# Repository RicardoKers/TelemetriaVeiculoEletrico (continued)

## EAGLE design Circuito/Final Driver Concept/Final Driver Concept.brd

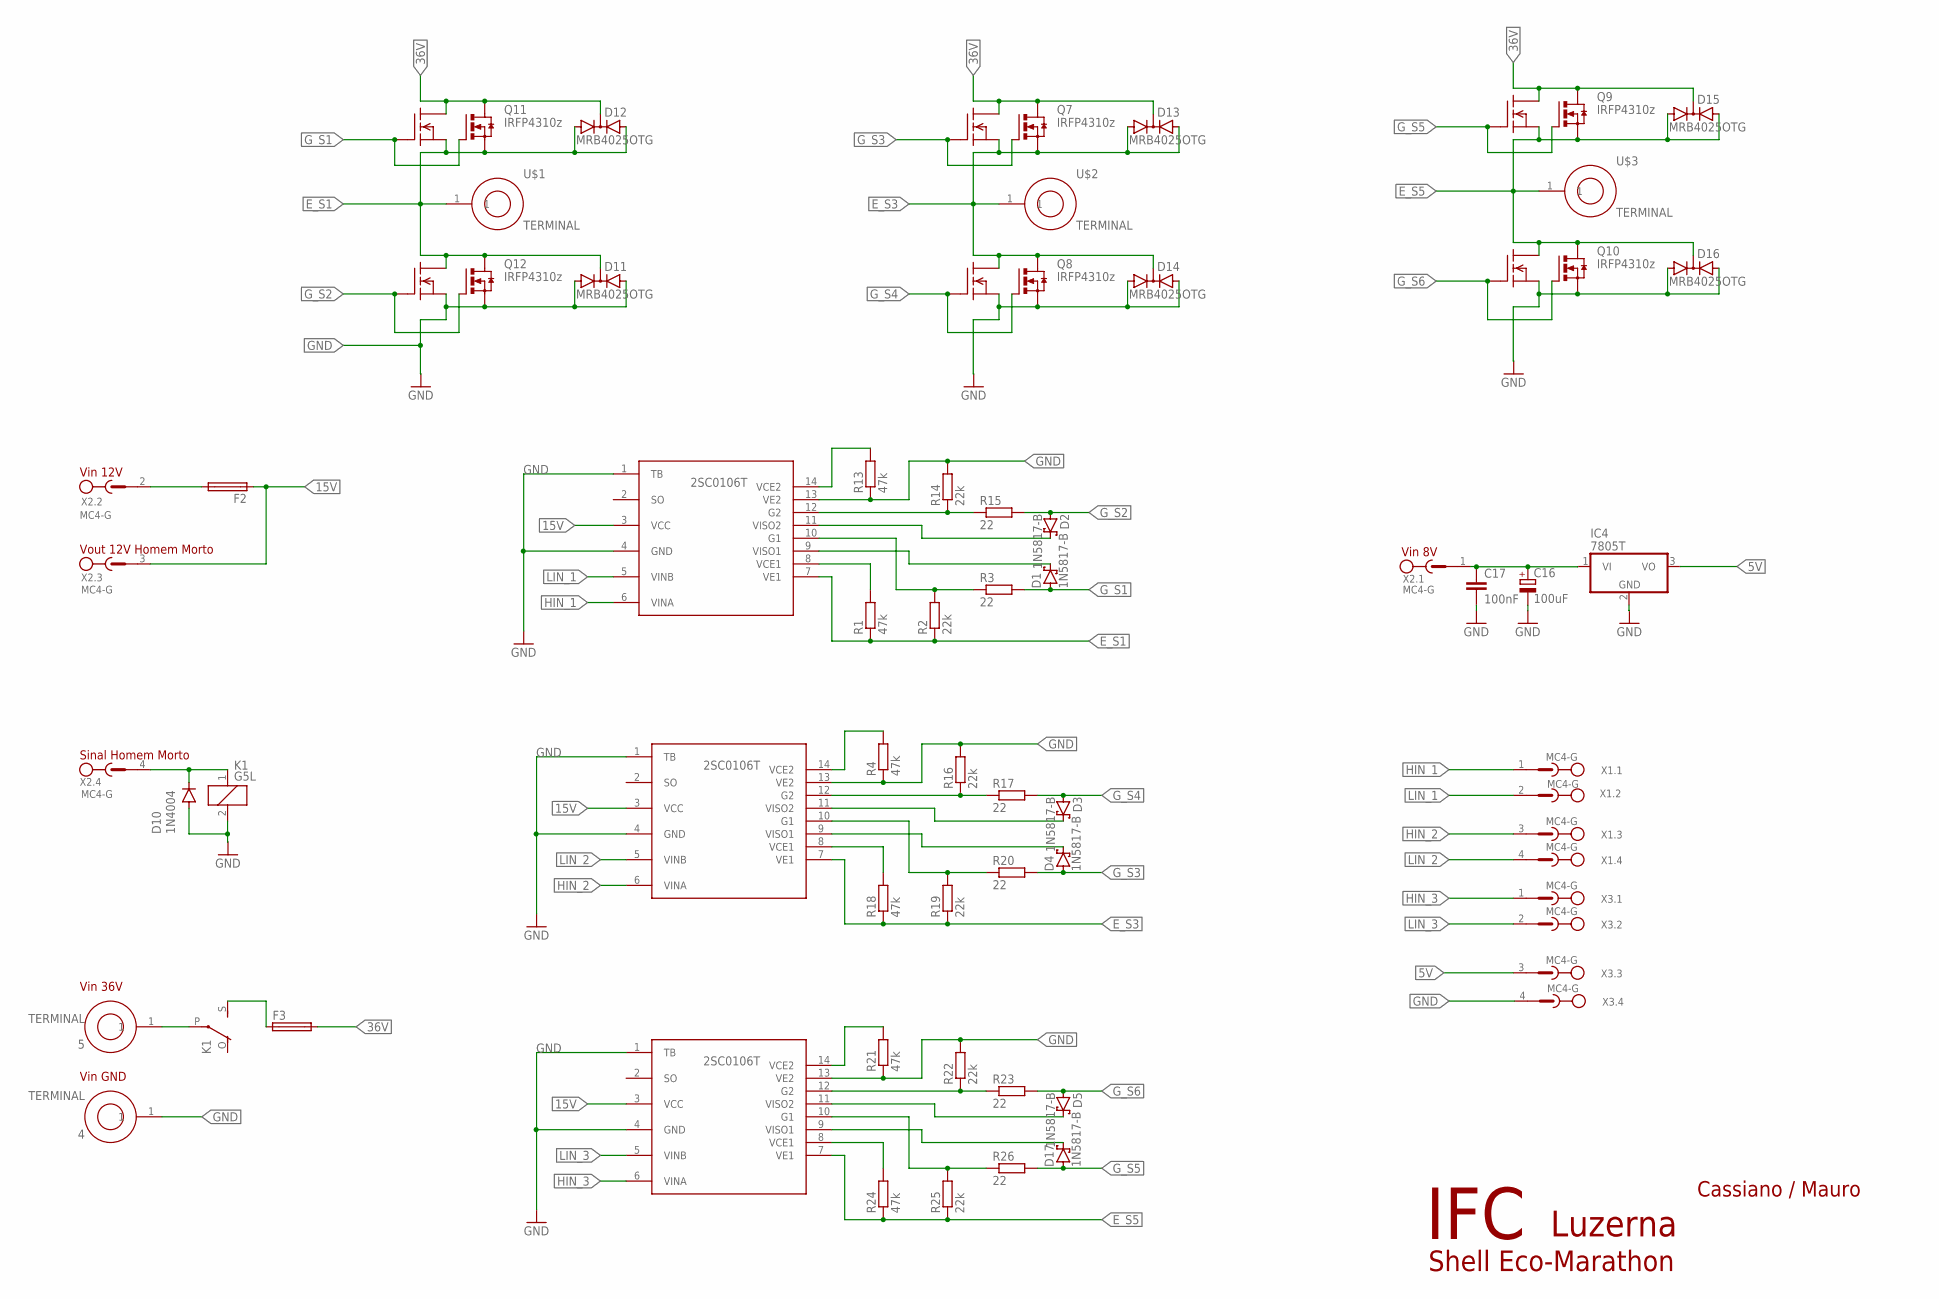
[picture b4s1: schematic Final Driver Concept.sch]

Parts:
4, 5: TERMINAL
C16: 100uF; E2,5-7
C17: 100nF; C050-045X075
D1, D2, D3, D4, D5, D17: 1N5817-B; DO41-7.6
D10: 1N4004; DO41-10
D11, D12, D13, D14, D15, D16: MRB4025OTG; TO220AB
F2, F3: SH22,5A
GATEDRIVER1, GATEDRIVER2, GATEDRIVER3: 2SC0106T1; 2SC0106T
IC4: 7805T; TO220H
K1: G5L; G5LE
Q1, Q2, Q3, Q4, Q5, Q6: IRF540; TO220
Q7, Q8, Q9, Q10, Q11, Q12: IRFP4310z; TO247BH
R1, R4, R13, R18, R21, R24: 47k; 0204/7
R2, R14, R16, R19, R22, R25: 22k; 0204/7
R3, R15, R17, R20, R23, R26: 22; 0204/7
U$1, U$2, U$3: TERMINAL
X1, X2, X3: MC4-G

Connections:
5V: IC4.3 (VO), X3.3
15V: F2.1, GATEDRIVER1.3 (VCC), GATEDRIVER2.3 (VCC), GATEDRIVER3.3 (VCC), X2.3
36V: D12.C, D13.C, D15.C, F3.2, Q1.2 (D), Q3.2 (D), Q5.2 (D), Q7.D, Q9.D, Q11.D
E_S1: D11.C, D12.A1, D12.A2, GATEDRIVER1.7 (VE1), Q1.3 (S), Q2.2 (D), Q11.S, Q12.D, R1.1, R2.1, U$1.1
E_S3: D13.A1, D13.A2, D14.C, GATEDRIVER2.7 (VE1), Q3.3 (S), Q4.2 (D), Q7.S, Q8.D, R18.1, R19.1, U$2.1
E_S5: D15.A1, D15.A2, D16.C, GATEDRIVER3.7 (VE1), Q5.3 (S), Q6.2 (D), Q9.S, Q10.D, R24.1, R25.1, U$3.1
GND: 4.1, C16.-, C17.2, D10.A, D11.A1, D11.A2, D14.A1, D14.A2, D16.A1, D16.A2, GATEDRIVER1.1 (TB), GATEDRIVER1.4 (GND), GATEDRIVER1.13 (VE2), GATEDRIVER2.1 (TB), GATEDRIVER2.4 (GND), GATEDRIVER2.13 (VE2), GATEDRIVER3.1 (TB), GATEDRIVER3.4 (GND), GATEDRIVER3.13 (VE2), IC4.2 (GND), K1.2, Q2.3 (S), Q4.3 (S), Q6.3 (S), Q8.S, Q10.S, Q12.S, R4.1, R13.1, R14.2, R16.2, R21.1, R22.2, X3.4
G_S1: D1.A, Q1.1 (G), Q11.G, R3.2
G_S2: D2.A, Q2.1 (G), Q12.G, R15.2
G_S3: D4.A, Q3.1 (G), Q7.G, R20.2
G_S4: D3.A, Q4.1 (G), Q8.G, R17.2
G_S5: D17.A, Q5.1 (G), Q9.G, R26.2
G_S6: D5.A, Q6.1 (G), Q10.G, R23.2
HIN_1: GATEDRIVER1.6 (VINA), X1.1
HIN_2: GATEDRIVER2.6 (VINA), X1.3
HIN_3: GATEDRIVER3.6 (VINA), X3.1
LIN_1: GATEDRIVER1.5 (VINB), X1.2
LIN_2: GATEDRIVER2.5 (VINB), X1.4
LIN_3: GATEDRIVER3.5 (VINB), X3.2
unnamed: GATEDRIVER2.14 (VCE2), R4.2
unnamed: D1.C, GATEDRIVER1.9 (VISO1)
unnamed: F3.1, K1.S
unnamed: F2.2, X2.2
unnamed: C16.+, C17.1, IC4.1 (VI), X2.1
unnamed: D10.C, K1.1, X2.4
unnamed: 5.1, K1.P
unnamed: GATEDRIVER1.14 (VCE2), R13.2
unnamed: GATEDRIVER1.12 (G2), R14.1, R15.1
unnamed: GATEDRIVER1.8 (VCE1), R1.2
unnamed: D2.C, GATEDRIVER1.11 (VISO2)
unnamed: GATEDRIVER1.10 (G1), R2.2, R3.1
unnamed: GATEDRIVER2.12 (G2), R16.1, R17.1
unnamed: D3.C, GATEDRIVER2.11 (VISO2)
unnamed: GATEDRIVER2.8 (VCE1), R18.2
unnamed: D4.C, GATEDRIVER2.9 (VISO1)
unnamed: GATEDRIVER2.10 (G1), R19.2, R20.1
unnamed: GATEDRIVER3.14 (VCE2), R21.2
unnamed: GATEDRIVER3.12 (G2), R22.1, R23.1
unnamed: D5.C, GATEDRIVER3.11 (VISO2)
unnamed: GATEDRIVER3.8 (VCE1), R24.2
unnamed: D17.C, GATEDRIVER3.9 (VISO1)
unnamed: GATEDRIVER3.10 (G1), R25.2, R26.1

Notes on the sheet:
Vin 8V
Vin 12V
Vout 12V Homem Morto
Sinal Homem Morto
Vin 36V
Vin GND
Shell Eco-Marathon
Cassiano / Mauro
IFC
Luzerna

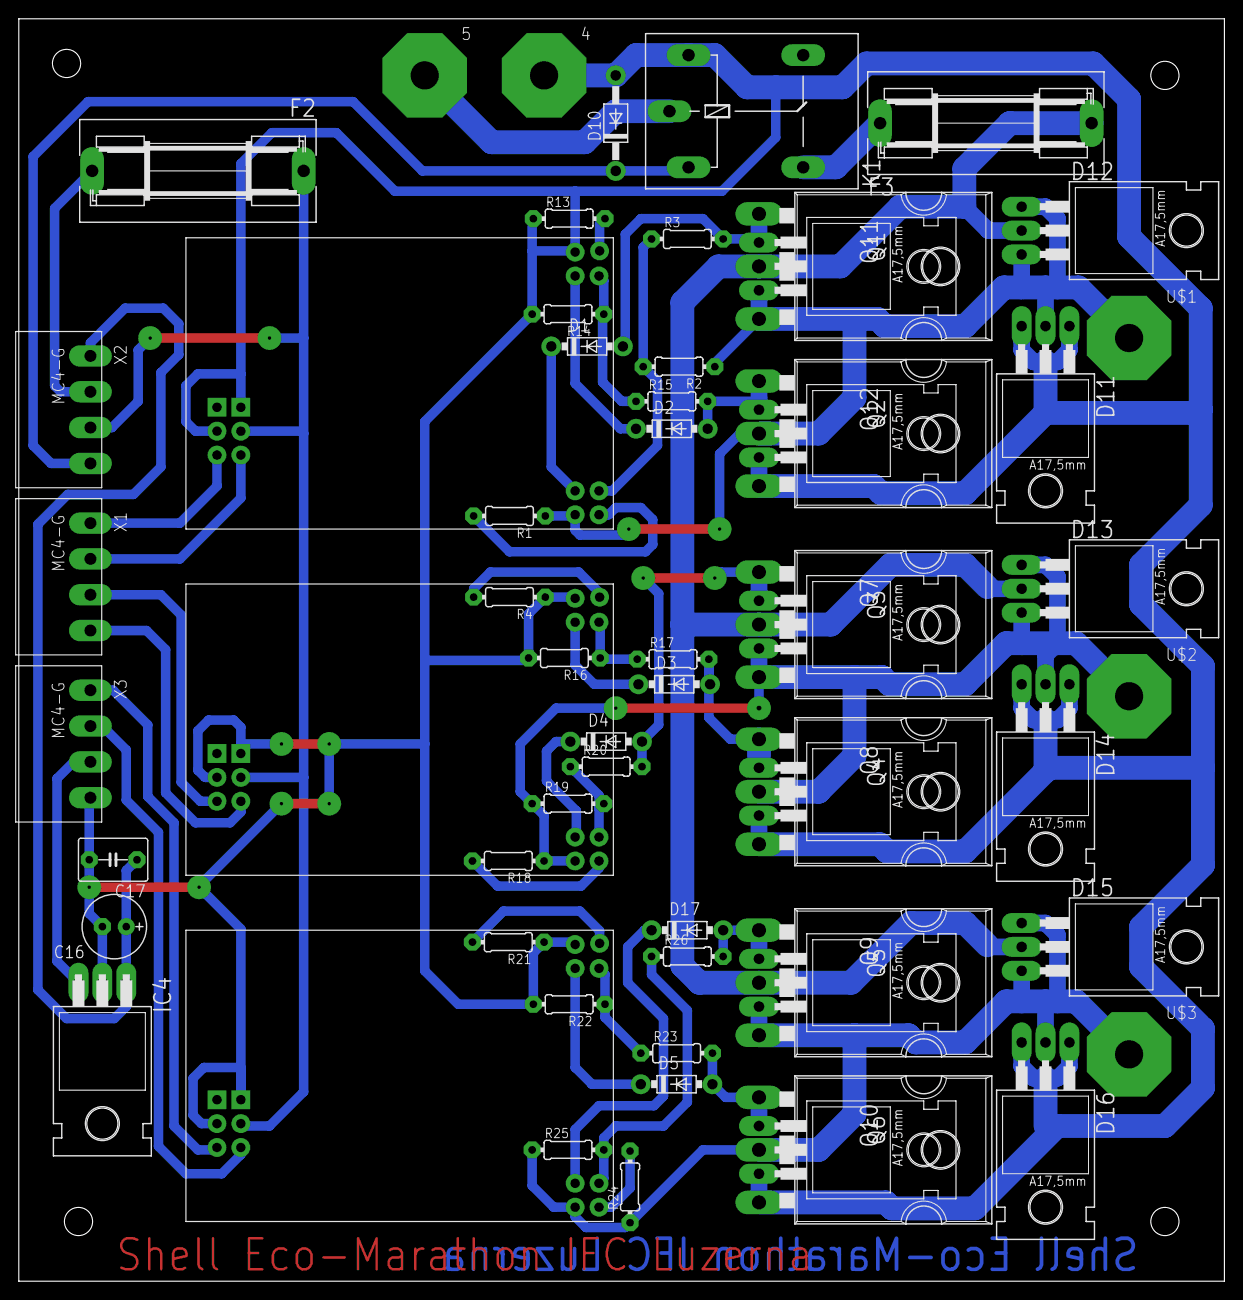
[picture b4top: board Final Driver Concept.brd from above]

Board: 2 copper layers, 128.2 x 134.3 mm, 60 parts (0 on the bottom side), 42 nets.

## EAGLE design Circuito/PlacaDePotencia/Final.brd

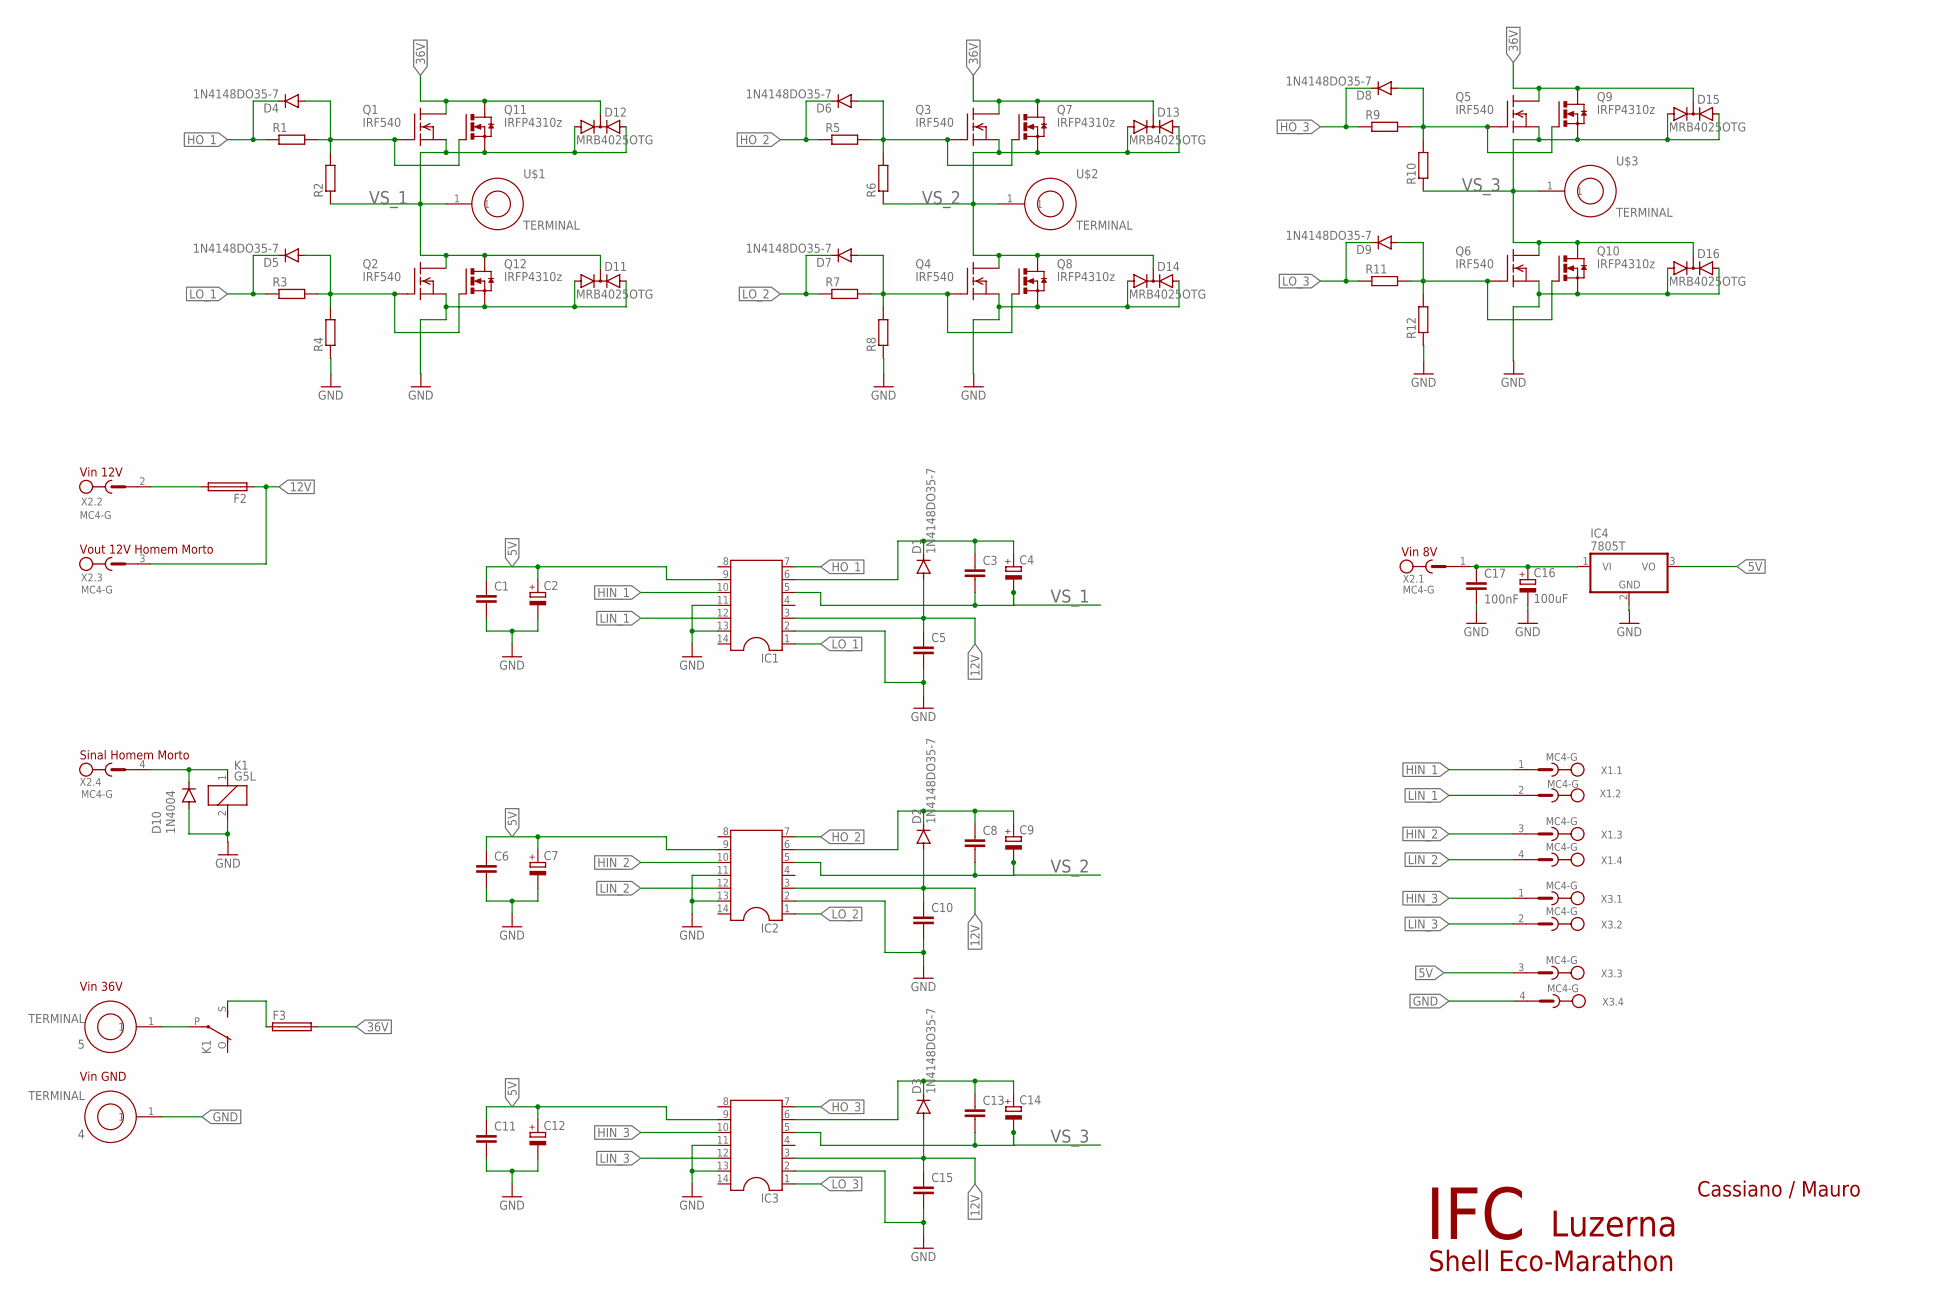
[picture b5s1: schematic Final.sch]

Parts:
4, 5: TERMINAL
C1, C6, C11: C-EU050-045X075; C050-045X075
C2, C4, C7, C9, C12, C14: CPOL-EUE2.5-7; E2,5-7
C3, C5, C8, C10, C13, C15: C-EU050-025X075; C050-025X075
C16: 100uF; E2,5-7
C17: 100nF; C050-045X075
D1, D2, D3, D4, D5, D6, D7, D8, D9: 1N4148DO35-7; DO35-7
D10: 1N4004; DO41-10
D11, D12, D13, D14, D15, D16: MRB4025OTG; TO220AB
F2, F3: SH22,5A
IC1, IC2, IC3: DIL14
IC4: 7805T; TO220H
K1: G5L; G5LE
Q1, Q2, Q3, Q4, Q5, Q6: IRF540; TO220
Q7, Q8, Q9, Q10, Q11, Q12: IRFP4310z; TO247BH
R1, R2, R3, R4, R5, R6, R7, R8, R9, R10, R11, R12: R-EU_0204/7; 0204/7
U$1, U$2, U$3: TERMINAL
X1, X2, X3: MC4-G

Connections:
5V: C1.1, C2.+, C6.1, C7.+, C11.1, C12.+, IC1.9, IC2.9, IC3.9, IC4.3 (VO), X3.3
12V: C5.1, C10.1, C15.1, D1.A, D2.A, D3.A, F2.1, IC1.3, IC2.3, IC3.3, X2.3
36V: D12.C, D13.C, D15.C, F3.2, Q1.2 (D), Q3.2 (D), Q5.2 (D), Q7.D, Q9.D, Q11.D
GND: 4.1, C1.2, C2.-, C5.2, C6.2, C7.-, C10.2, C11.2, C12.-, C15.2, C16.-, C17.2, D10.A, D11.A1, D11.A2, D14.A1, D14.A2, D16.A1, D16.A2, IC1.2, IC1.11, IC1.13, IC2.2, IC2.11, IC2.13, IC3.2, IC3.11, IC3.13, IC4.2 (GND), K1.2, Q2.3 (S), Q4.3 (S), Q6.3 (S), Q8.S, Q10.S, Q12.S, R4.1, R8.1, R12.1, X3.4
HIN_1: IC1.10, X1.1
HIN_2: IC2.10, X1.3
HIN_3: IC3.10, X3.1
HO_1: D4.C, IC1.7, R1.1
HO_2: D6.C, IC2.7, R5.1
HO_3: D8.C, IC3.7, R9.1
LIN_1: IC1.12, X1.2
LIN_2: IC2.12, X1.4
LIN_3: IC3.12, X3.2
LO_1: D5.C, IC1.1, R3.1
LO_2: D7.C, IC2.1, R7.1
LO_3: D9.C, IC3.1, R11.1
unnamed: D4.A, Q1.1 (G), Q11.G, R1.2, R2.2
unnamed: D5.A, Q2.1 (G), Q12.G, R3.2, R4.2
unnamed: F3.1, K1.S
unnamed: D6.A, Q3.1 (G), Q7.G, R5.2, R6.2
unnamed: D7.A, Q4.1 (G), Q8.G, R7.2, R8.2
unnamed: F2.2, X2.2
unnamed: D8.A, Q5.1 (G), Q9.G, R9.2, R10.2
unnamed: D9.A, Q6.1 (G), Q10.G, R11.2, R12.2
unnamed: C16.+, C17.1, IC4.1 (VI), X2.1
unnamed: D10.C, K1.1, X2.4
unnamed: 5.1, K1.P
VB_1: C3.1, C4.+, D1.C, IC1.6
VB_2: C8.1, C9.+, D2.C, IC2.6
VB_3: C13.1, C14.+, D3.C, IC3.6
VS_1: C3.2, C4.-, D11.C, D12.A1, D12.A2, IC1.5, Q1.3 (S), Q2.2 (D), Q11.S, Q12.D, R2.1, U$1.1
VS_2: C8.2, C9.-, D13.A1, D13.A2, D14.C, IC2.5, Q3.3 (S), Q4.2 (D), Q7.S, Q8.D, R6.1, U$2.1
VS_3: C13.2, C14.-, D15.A1, D15.A2, D16.C, IC3.5, Q5.3 (S), Q6.2 (D), Q9.S, Q10.D, R10.1, U$3.1

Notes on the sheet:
Vin 8V
Vin 12V
Vout 12V Homem Morto
Sinal Homem Morto
Vin 36V
Vin GND
Shell Eco-Marathon
Cassiano / Mauro
IFC
Luzerna

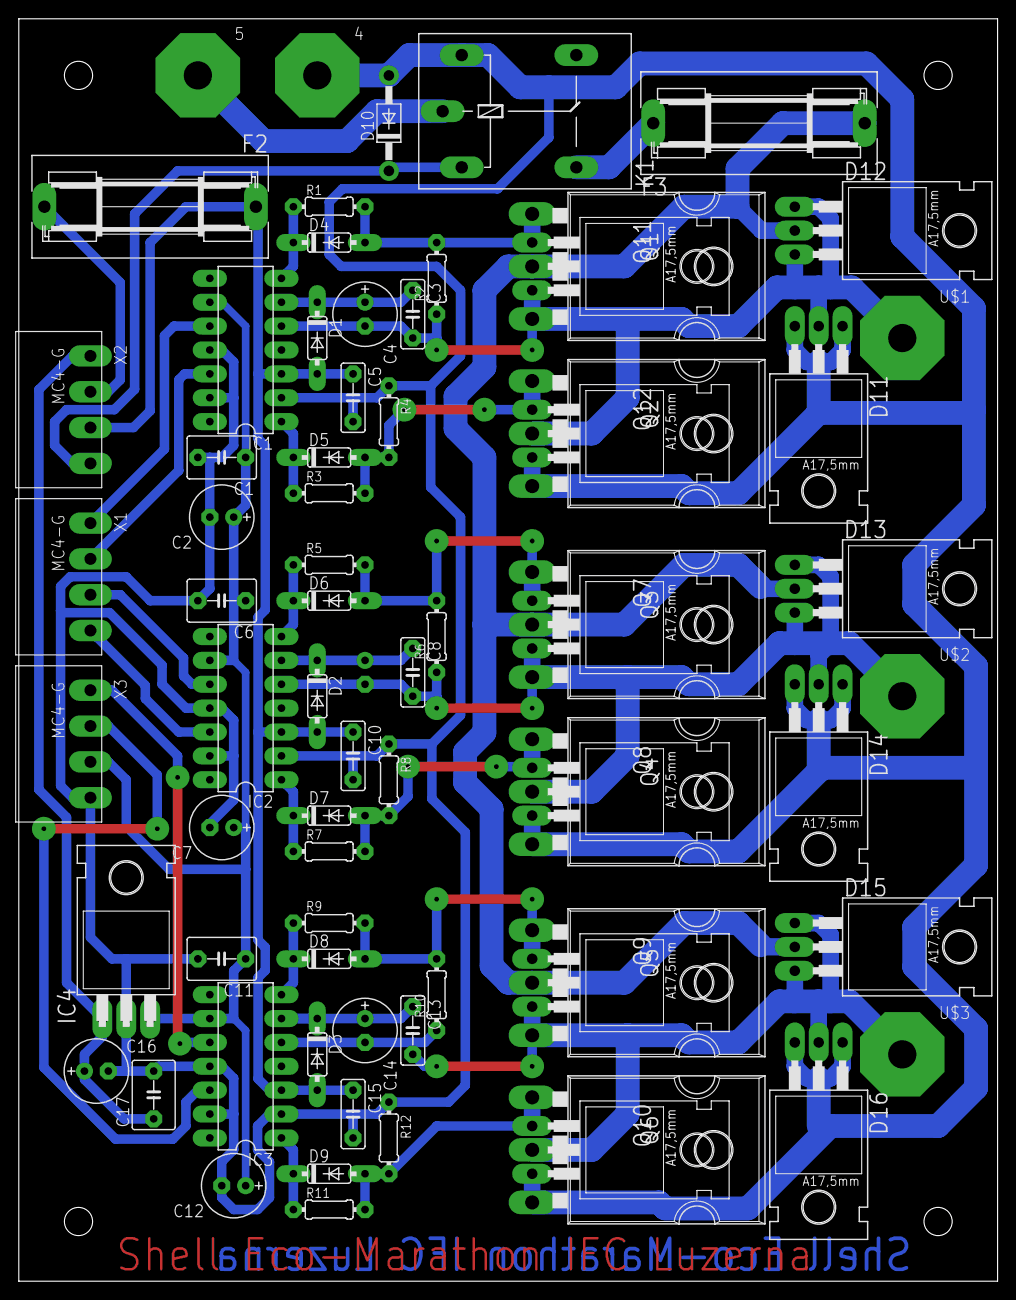
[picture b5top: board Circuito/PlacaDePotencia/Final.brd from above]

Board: 2 copper layers, 104.1 x 134.3 mm, 72 parts (1 on the bottom side), 33 nets.

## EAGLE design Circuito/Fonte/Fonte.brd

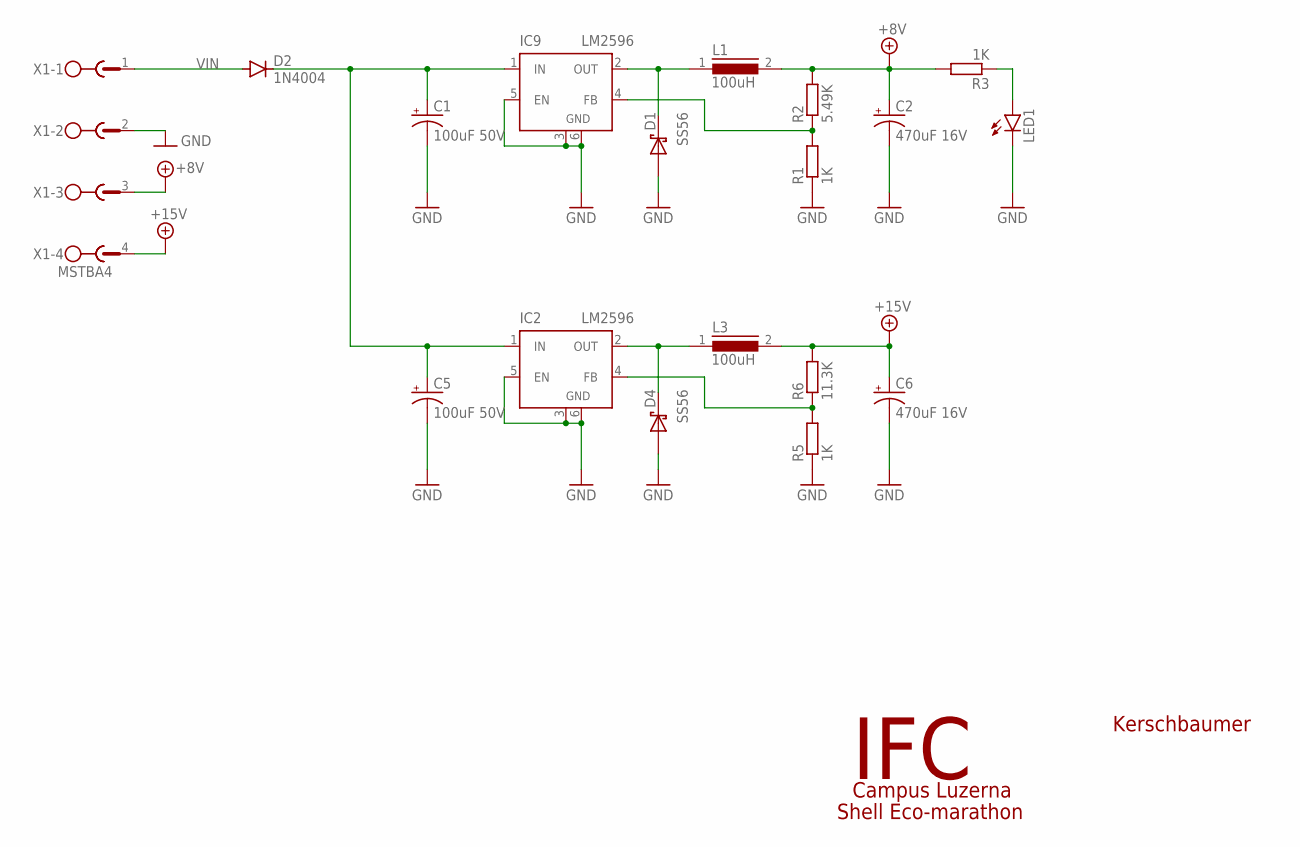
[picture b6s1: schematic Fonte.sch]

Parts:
C1, C5: 100uF 50V; E2,5-7
C2, C6: 470uF 16V; E2,5-7
D1, D4: SS56; SMA-DIODE
D2: 1N4004; DO41-10
IC2, IC9: LM2596; TO263-5
L1, L3: 100uH; DR125
LED1: LED3MM
R1, R3, R5: 1K; 0207/7
R2: 5.49K; 0207/7
R6: 11.3K; 0207/7
X1: MSTBA4

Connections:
+8V: C2.+, L1.2, R2.2, R3.2, X1.3
+15V: C6.+, L3.2, R6.2, X1.4
GND: C1.-, C2.-, C5.-, C6.-, D1.A, D4.A, IC2.3 (GND), IC2.5 (EN), IC2.6 (GND), IC9.3 (GND), IC9.5 (EN), IC9.6 (GND), LED1.K (C), R1.1, R5.1, X1.2
unnamed: C1.+, C5.+, D2.C, IC2.1 (IN), IC9.1 (IN)
unnamed: IC9.4 (FB), R1.2, R2.1
unnamed: D1.C, IC9.2 (OUT), L1.1
unnamed: LED1.A, R3.1
unnamed: IC2.4 (FB), R5.2, R6.1
unnamed: D4.C, IC2.2 (OUT), L3.1
VIN: D2.A, X1.1

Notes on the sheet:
Kerschbaumer
IFC
Shell Eco-marathon
Campus Luzerna

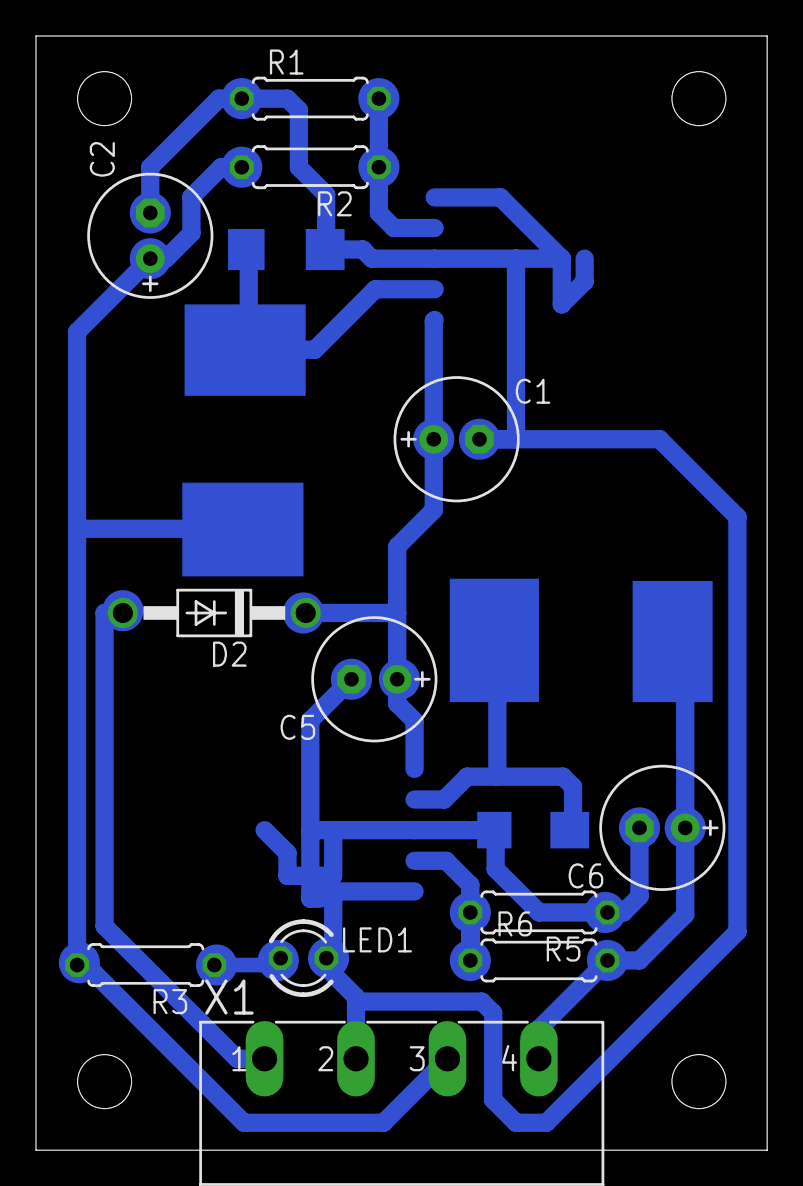
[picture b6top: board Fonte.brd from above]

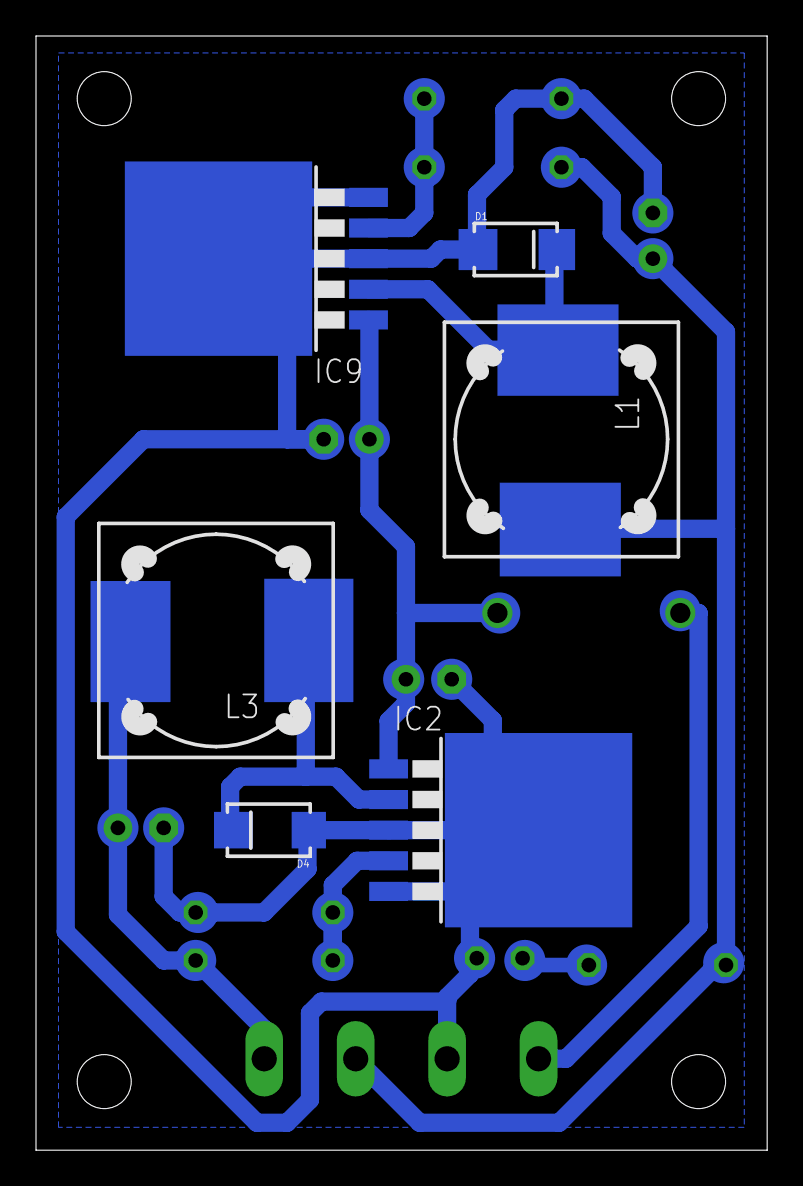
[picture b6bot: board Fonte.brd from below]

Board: 2 copper layers, 40.6 x 61.9 mm, 18 parts (6 on the bottom side), 10 nets.

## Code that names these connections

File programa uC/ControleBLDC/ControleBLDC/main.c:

/*
 * ControleBLDC.c
 * ATmega8
 * Created: 20/07/2022 19:11:07
 * Author : Kerschbaumer

 VERSÃO 0.6

Sinais BLDC

Chaves
Q1 Q3 Q5
Q2 Q4 Q8

states   0  1  2  3  4  5
Hall 1	"""""""""_________
Hall 2	______"""""""""___
Hall 3	"""_________""""""

Q1(PWM) MMMMMM____________
Q2		_________""""""___
Q3(PWM)	______MMMMMM______
Q4		"""____________"""
Q5(PWM)	____________MMMMMM
Q6		___""""""_________
  */ 

#include <avr/io.h>
#include <avr/interrupt.h>
#define F_CPU 8000000
#include <util/delay.h>

#define placaAntiga
//#define placaNova


#if defined(placaAntiga)
	#define Hall_1 (PIND & (1<<PD0))
	#define Hall_2 (PIND & (1<<PD1))
	#define Hall_3 (PIND & (1<<PD2))

	#define Q1_H (PORTB |= (1<<PB1))
	#define Q1_L (PORTB &= ~(1<<PB1))

	#define Q2_H (PORTD |= (1<<PD5))
	#define Q2_L (PORTD &= ~(1<<PD5))

	#define Q3_H (PORTB |= (1<<PB2))
	#define Q3_L (PORTB &= ~(1<<PB2))

	#define Q4_H (PORTD |= (1<<PD6))
	#define Q4_L (PORTD &= ~(1<<PD6))

	#define Q5_H (PORTB |= (1<<PB3))
	#define Q5_L (PORTB &= ~(1<<PB3))

	#define Q6_H (PORTD |= (1<<PD7))
	#define Q6_L (PORTD &= ~(1<<PD7))
#else
	#define Hall_1 (PINC & (1<<PC0))
	#define Hall_2 (PINC & (1<<PC1))
	#define Hall_3 (PINC & (1<<PC2))

	#define Q1_H (PORTB |= (1<<PB1))
	#define Q1_L (PORTB &= ~(1<<PB1))

	#define Q2_H (PORTB |= (1<<PB0))
	#define Q2_L (PORTB &= ~(1<<PB0))

	#define Q3_H (PORTB |= (1<<PB2))
	#define Q3_L (PORTB &= ~(1<<PB2))

	#define Q4_H (PORTB |= (1<<PB4))
	#define Q4_L (PORTB &= ~(1<<PB4))

	#define Q5_H (PORTB |= (1<<PB3))
	#define Q5_L (PORTB &= ~(1<<PB3))

	#define Q6_H (PORTB |= (1<<PB5))
	#define Q6_L (PORTB &= ~(1<<PB5))
#endif

enum states {E0, E1, E2, E3, E4, E5};
enum states state;
enum states oldState;

int entAna0;

void getHallState()
{
	char hallState=0;
	if(Hall_1 != 0) hallState += 1;
	if(Hall_2 != 0) hallState += 2;
	if(Hall_3 != 0) hallState += 4;
	
	switch (hallState)
	{
		case 1:
			state = E1;
		break;
		case 2:
			state = E3;
		break;
		case 3:
			state = E2;
		break;
		case 4:
			state = E5;
		break;
		case 5:
			state = E0;
		break;
		case 6:
			state = E4;
		break;
	}
}

ISR(TIMER1_COMPA_vect)
{
	Q1_L;
	Q5_L;
	Q3_L;
}

ISR(TIMER1_OVF_vect)
{
	OCR1A=entAna0;
	TCNT1=0;
	if(entAna0>3)
	{
		switch (state)
		{
			case E0:
			Q1_H;
			break;
			case E1:
			Q1_H;
			break;
			case E2:
			Q3_H;
			break;
			case E3:
			Q3_H;
			break;
			case E4:
			Q5_H;
			break;
			case E5:
			Q5_H;
			break;
		}
	}
}

ISR(ADC_vect)
{
	entAna0=ADCW/2;
	if(entAna0>501) entAna0=501;
	ADCSRA|=0b01000000; // inicia nova conversão
}

int main(void)
{
	ICR1 = 499; // Divide o clock por 1000 (ICR1+1) para um PWM de 1 KHz
	OCR1A=0; // Ajusta o PWM inicial para 0%
	TCCR1A = (1 << WGM11); // Ajusta para o modo PWM Rápido
	TCCR1B = (1 << WGM12) | (1 << WGM13) | (1 << CS10); // Ajusta o prescaler para 1
	TIMSK  = (1 << OCIE1A) | (1 << TOIE1); // habilita as interrupções
	
	#if defined(placaAntiga)
		DDRB = 0b00001110;
		DDRD = 0b11100000;
		ADMUX=0b01000000; // escolhe a entrada analógica 0, com a referência no pino AVCC
	#else
		DDRB = 0b00111111;
		DDRD = 0b00000000;
		ADMUX=0b01000011; // escolhe a entrada analógica 0, com a referência no pino AVCC
	#endif  
	 
	ADCSRA=0b11001111; // habilita o A/D com prescaler de 128, habilitando sua interrupção.
	
	sei();
	
    while (1) 
    {
		cli();
		getHallState();	
		if(state!=oldState)
		{
			oldState=state;
			Q1_L;
			Q5_L;
			Q3_L;
			switch (state)
			{
				case E0:
				Q4_H;
				Q2_L;
				Q6_L;
				break;
				case E1:
				Q6_H;
				Q4_L;
				Q2_L;
				break;
				case E2:
				Q6_H;
				Q4_L;
				Q2_L;
				break;
				case E3:
				Q2_H;
				Q4_L;
				Q6_L;
				break;
				case E4:
				Q2_H;
				Q4_L;
				Q6_L;
				break;
				case E5:
				Q4_H;
				Q2_L;
				Q6_L;
				break;
			}
			TCNT1=0;
		}		
		sei();
    }
}

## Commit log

2019-04-07 Códigos iniciais
2019-05-16 mais testes
2022-04-19 Atualizando...
2022-08-31 versão 2022
